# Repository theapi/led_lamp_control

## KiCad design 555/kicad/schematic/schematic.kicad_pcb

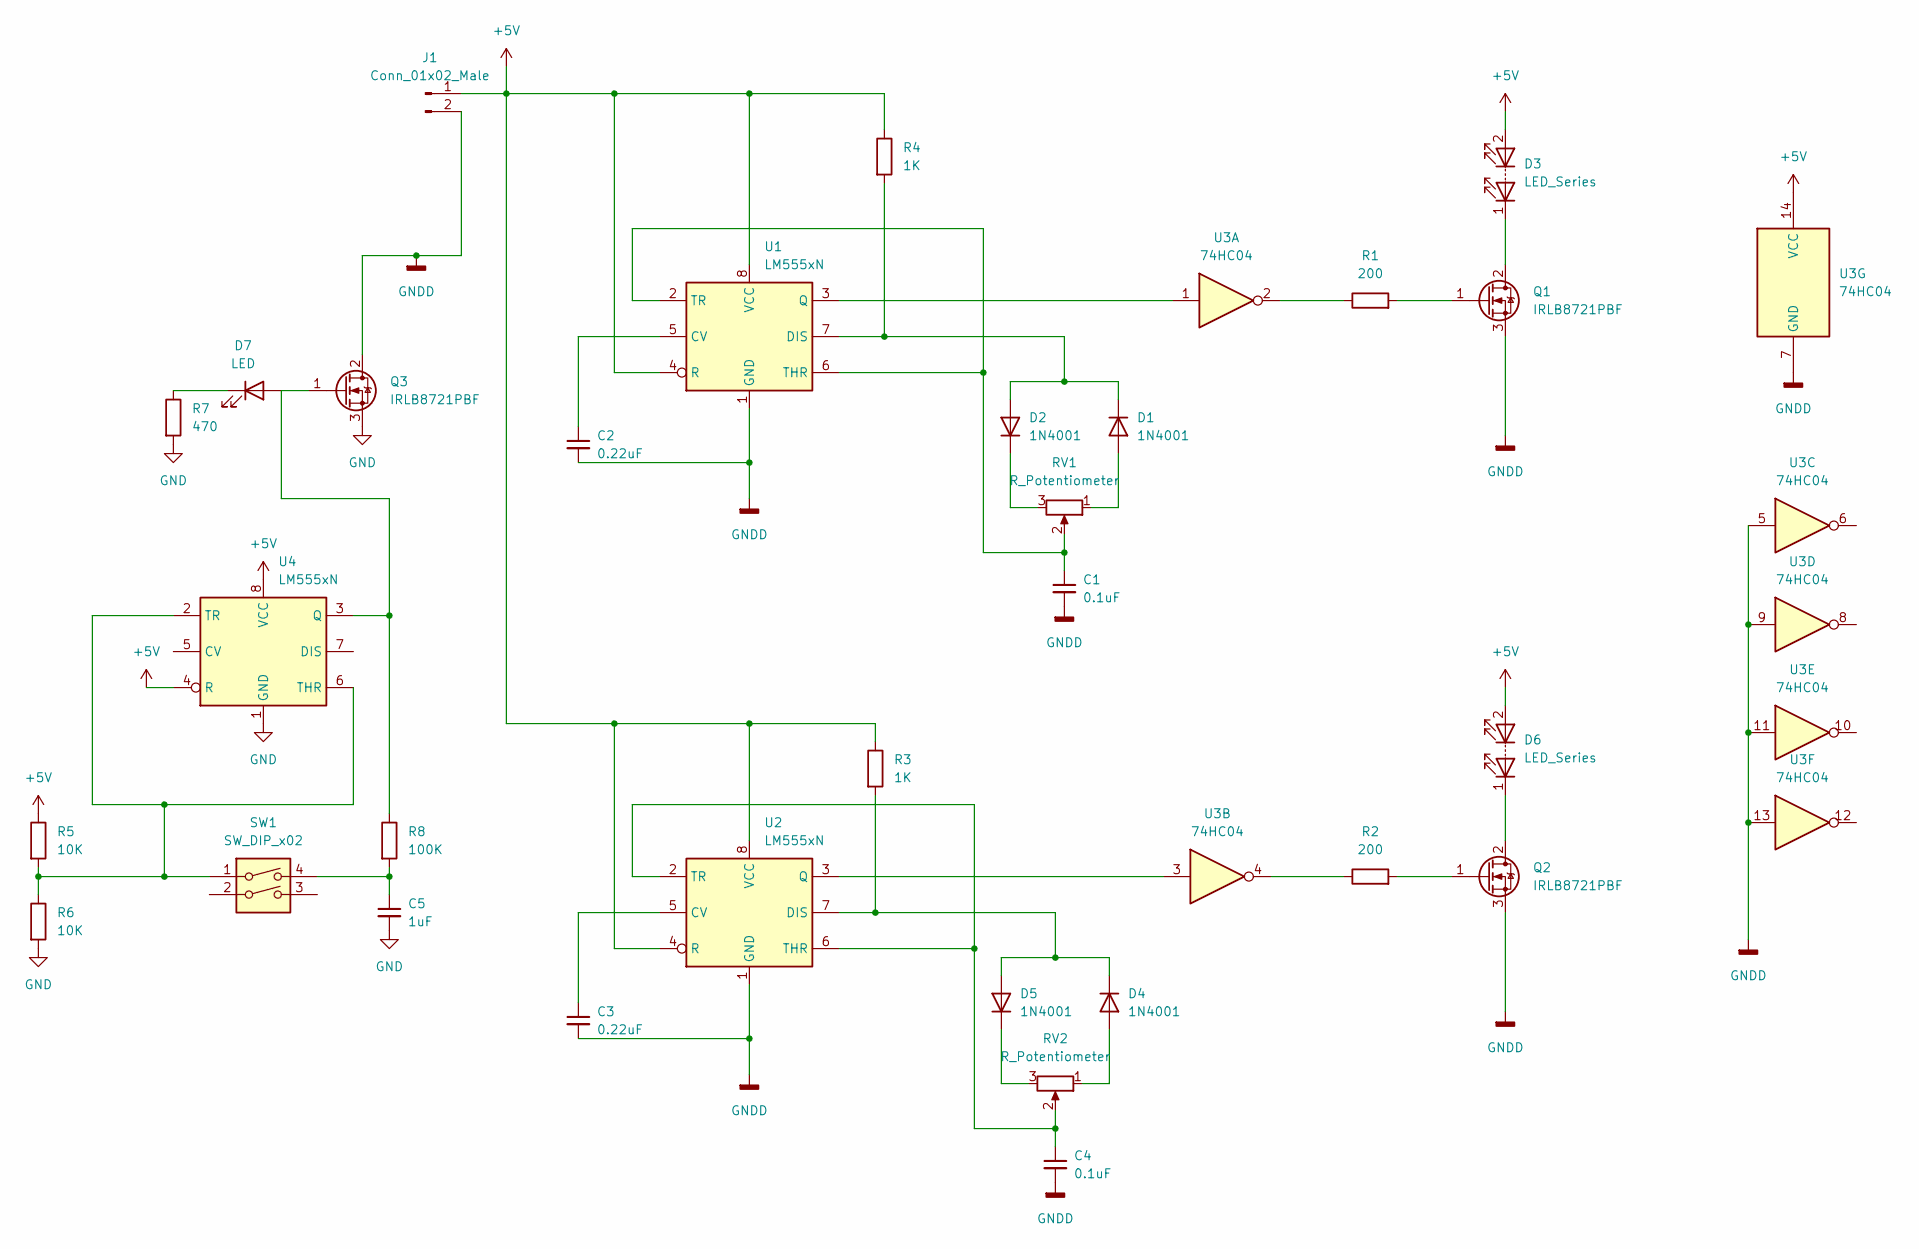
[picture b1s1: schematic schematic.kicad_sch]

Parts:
C1, C4: 0.1uF; C_Disc_D9.0mm_W2.5mm_P5.00mm
C2, C3: 0.22uF; C_Disc_D9.0mm_W2.5mm_P5.00mm
C5: 1uF; C_Disc_D9.0mm_W2.5mm_P5.00mm
D1, D2, D4, D5: 1N4001; D_DO-41_SOD81_P10.16mm_Horizontal
D3, D6: LED_Series; PinHeader_1x02_P2.54mm_Vertical
D7: LED; LED_D5.0mm
J1: Conn_01x02_Male; PinHeader_1x02_P2.54mm_Vertical
Q1, Q2, Q3: IRLB8721PBF; TO-220-3_Vertical
R1, R2: 200; R_Axial_DIN0207_L6.3mm_D2.5mm_P10.16mm_Horizontal
R3, R4: 1K; R_Axial_DIN0207_L6.3mm_D2.5mm_P10.16mm_Horizontal
R5, R6: 10K; R_Axial_DIN0207_L6.3mm_D2.5mm_P10.16mm_Horizontal
R7: 470; R_Axial_DIN0207_L6.3mm_D2.5mm_P10.16mm_Horizontal
R8: 100K; R_Axial_DIN0207_L6.3mm_D2.5mm_P10.16mm_Horizontal
RV1, RV2: R_Potentiometer; Potentiometer_Alps_RK163_Single_Horizontal
SW1: SW_DIP_x02; SW_PUSH_6mm
U1, U2, U4: LM555xN; DIP-8_W7.62mm
U3: 74HC04; DIP-14_W7.62mm_LongPads

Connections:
+5V: D3.2 (A), D6.2 (A), J1.1, R3.1, R4.1, R5.1, U1.4 (R), U1.8 (VCC), U2.4 (R), U2.8 (VCC), U3.14 (VCC), U4.4 (R), U4.8 (VCC)
GND: C5.2, Q3.3 (S), R6.2, R7.2, U4.1 (GND)
GNDD: C1.2, C2.2, C3.2, C4.2, J1.2, Q1.3 (S), Q2.3 (S), Q3.2 (D), U1.1 (GND), U2.1 (GND), U3.5, U3.7 (GND), U3.9, U3.11, U3.13
unnamed: C1.1, RV1.2, U1.2 (TR), U1.6 (THR)
unnamed: C2.1, U1.5 (CV)
unnamed: C3.1, U2.5 (CV)
unnamed: C4.1, RV2.2, U2.2 (TR), U2.6 (THR)
unnamed: C5.1, R8.2, SW1.4
unnamed: D1.1 (K), D2.2 (A), R4.2, U1.7 (DIS)
unnamed: D1.2 (A), RV1.1
unnamed: D2.1 (K), RV1.3
unnamed: D3.1 (K), Q1.2 (D)
unnamed: D4.1 (K), D5.2 (A), R3.2, U2.7 (DIS)
unnamed: D4.2 (A), RV2.1
unnamed: D5.1 (K), RV2.3
unnamed: D6.1 (K), Q2.2 (D)
unnamed: D7.1 (K), R7.1
unnamed: D7.2 (A), Q3.1 (G), R8.1, U4.3 (Q)
unnamed: Q1.1 (G), R1.2
unnamed: Q2.1 (G), R2.2
unnamed: R1.1, U3.2
unnamed: R2.1, U3.4
unnamed: R5.2, R6.1, SW1.1, U4.2 (TR), U4.6 (THR)
unnamed: U1.3 (Q), U3.1
unnamed: U2.3 (Q), U3.3

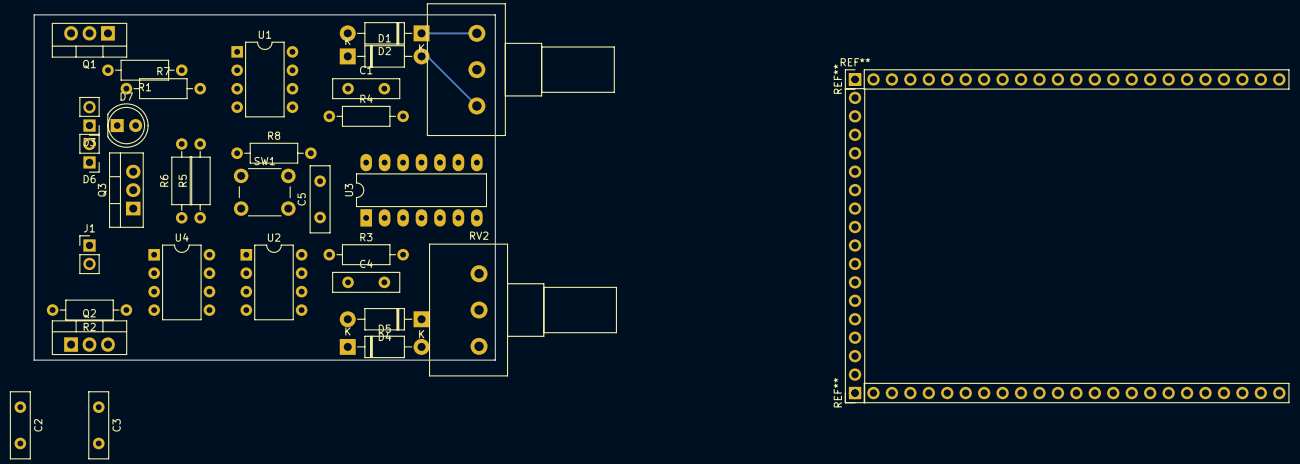
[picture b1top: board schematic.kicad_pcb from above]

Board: 2 copper layers, 63.5 x 47.5 mm, 31 parts (0 on the bottom side), 25 nets.
